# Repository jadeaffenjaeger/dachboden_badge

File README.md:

# Dachboden Robot Logo PCB badge

PCB Art badge using 2020 WS2812B SMD LEDs, attiny45 MCU and light_ws2812 library.

Detailed writeup can be found [here](https://etrommer.github.io/projects/electronics/2021/11/06/robot-badge.html)

## Programming

To build the firmware, you need the avr-gcc toolchain and a [USBtinyISP](https://learn.adafruit.com/usbtinyisp) (which you can buy for a few euros on AliExpress etc.)

```bash
cd firmware
make all
```
Then, with the programmer connected to the test points on the back of the badge, run:
```bash
make fuses
make program
```
to flash the firmware onto the badge.

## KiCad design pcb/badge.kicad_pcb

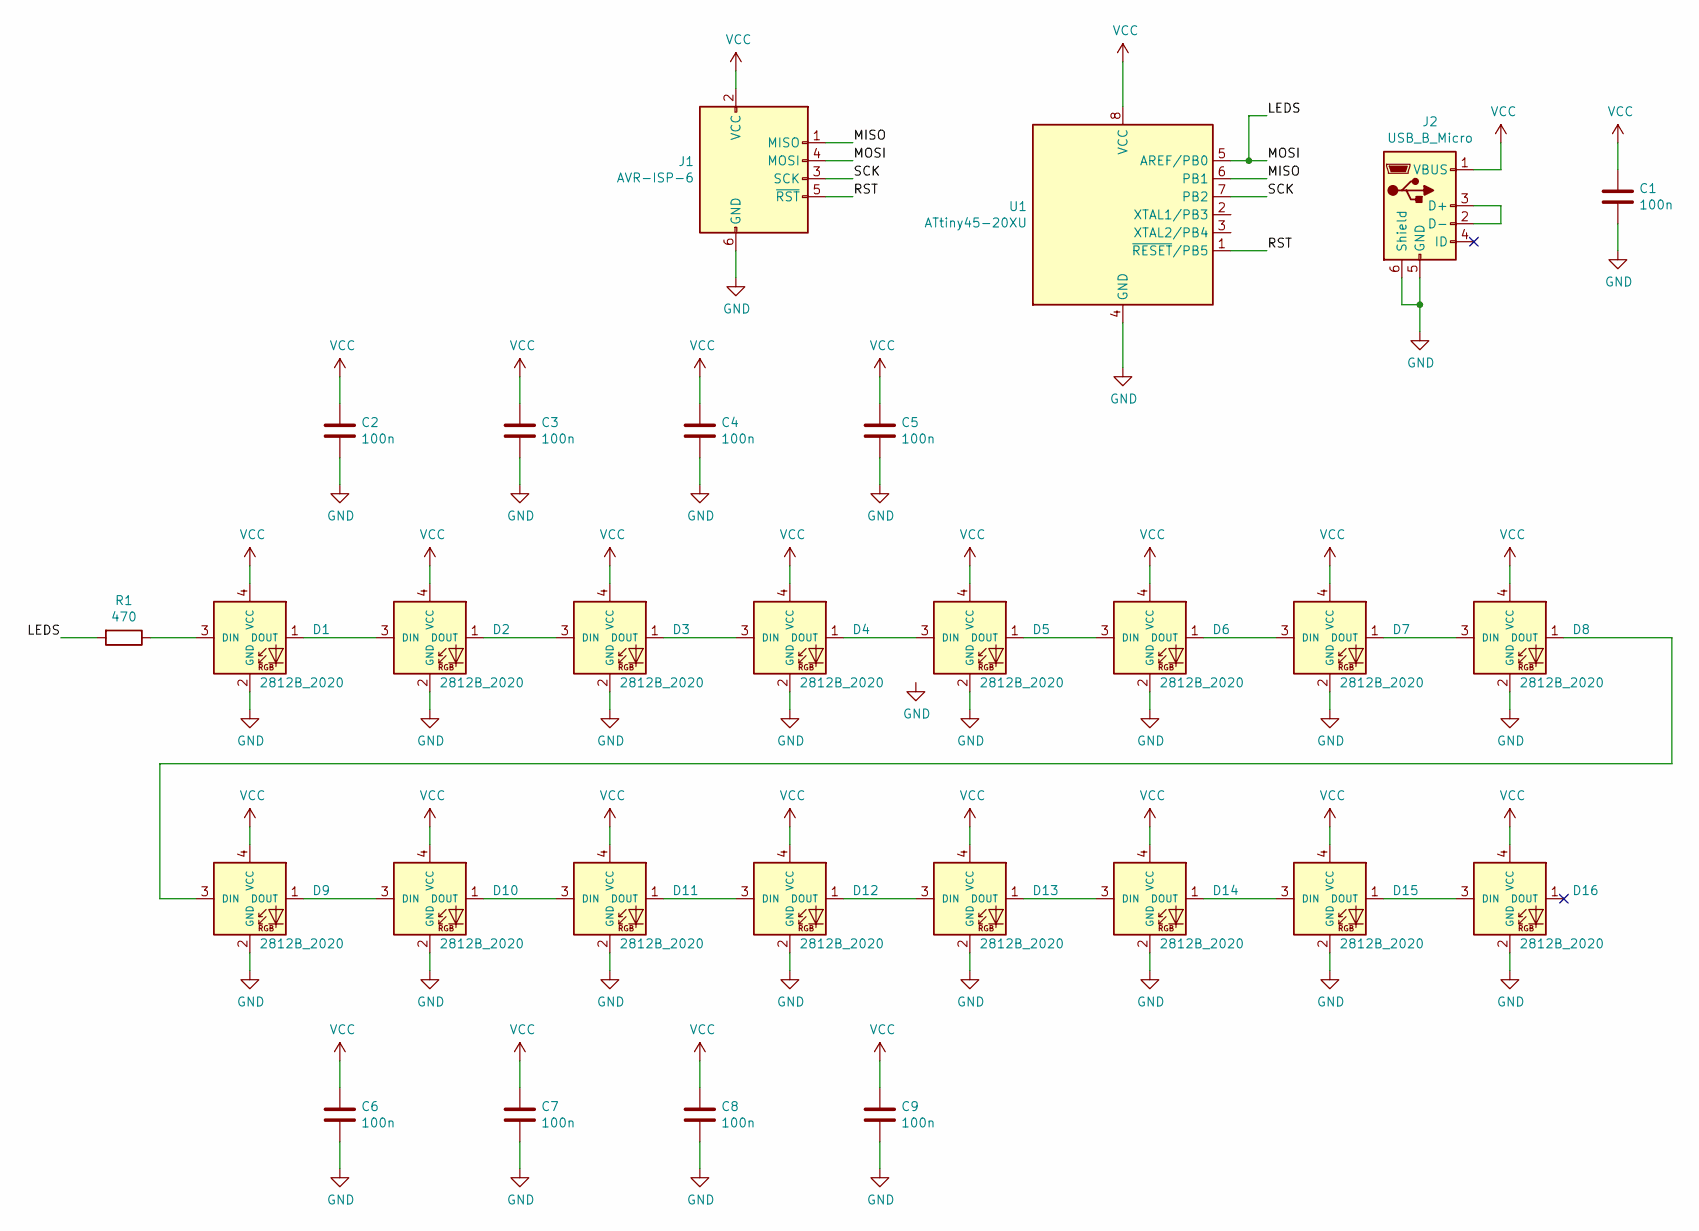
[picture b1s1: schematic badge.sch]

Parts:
C1, C2, C3, C4, C5, C6, C7, C8, C9: 100n; C_0402_1005Metric
D1, D2, D3, D4, D5, D6, D7, D8, D9, D10, D11, D12, D13, D14, D15, D16: 2812B_2020; ws2812_2020
J1: AVR-ISP-6; debug_header
J2: USB_B_Micro; micro_usb
R1: 470; R_0402_1005Metric
U1: ATtiny45-20XU; SOIJ-8_5.3x5.3mm_P1.27mm

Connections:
/LEDS: J1.4 (MOSI), R1.2, U1.5 (AREF/PB0)
/MISO: J1.1 (MISO), U1.6 (PB1)
/RST: J1.5 (~RST), U1.1 (~RESET~/PB5)
/SCK: J1.3 (SCK), U1.7 (PB2)
GND: C1.2, C2.2, C3.2, C4.2, C5.2, C6.2, C7.2, C8.2, C9.2, D1.2 (GND), D2.2 (GND), D3.2 (GND), D4.2 (GND), D5.2 (GND), D6.2 (GND), D7.2 (GND), D8.2 (GND), D9.2 (GND), D10.2 (GND), D11.2 (GND), D12.2 (GND), D13.2 (GND), D14.2 (GND), D15.2 (GND), D16.2 (GND), J1.6 (GND), J2.5 (GND), J2.6 (Shield), U1.4 (GND)
unnamed: D1.1 (DOUT), D2.3 (DIN)
unnamed: D1.3 (DIN), R1.1
unnamed: D2.1 (DOUT), D3.3 (DIN)
unnamed: D3.1 (DOUT), D4.3 (DIN)
unnamed: D4.1 (DOUT), D5.3 (DIN)
unnamed: D5.1 (DOUT), D6.3 (DIN)
unnamed: D6.1 (DOUT), D7.3 (DIN)
unnamed: D7.1 (DOUT), D8.3 (DIN)
unnamed: D8.1 (DOUT), D9.3 (DIN)
unnamed: D10.1 (DOUT), D11.3 (DIN)
unnamed: D9.1 (DOUT), D10.3 (DIN)
unnamed: D11.1 (DOUT), D12.3 (DIN)
unnamed: D12.1 (DOUT), D13.3 (DIN)
unnamed: D13.1 (DOUT), D14.3 (DIN)
unnamed: D14.1 (DOUT), D15.3 (DIN)
unnamed: D15.1 (DOUT), D16.3 (DIN)
unnamed: J2.2 (D-), J2.3 (D+)
VCC: C1.1, C2.1, C3.1, C4.1, C5.1, C6.1, C7.1, C8.1, C9.1, D1.4 (VCC), D2.4 (VCC), D3.4 (VCC), D4.4 (VCC), D5.4 (VCC), D6.4 (VCC), D7.4 (VCC), D8.4 (VCC), D9.4 (VCC), D10.4 (VCC), D11.4 (VCC), D12.4 (VCC), D13.4 (VCC), D14.4 (VCC), D15.4 (VCC), D16.4 (VCC), J1.2 (VCC), J2.1 (VBUS), U1.8 (VCC)

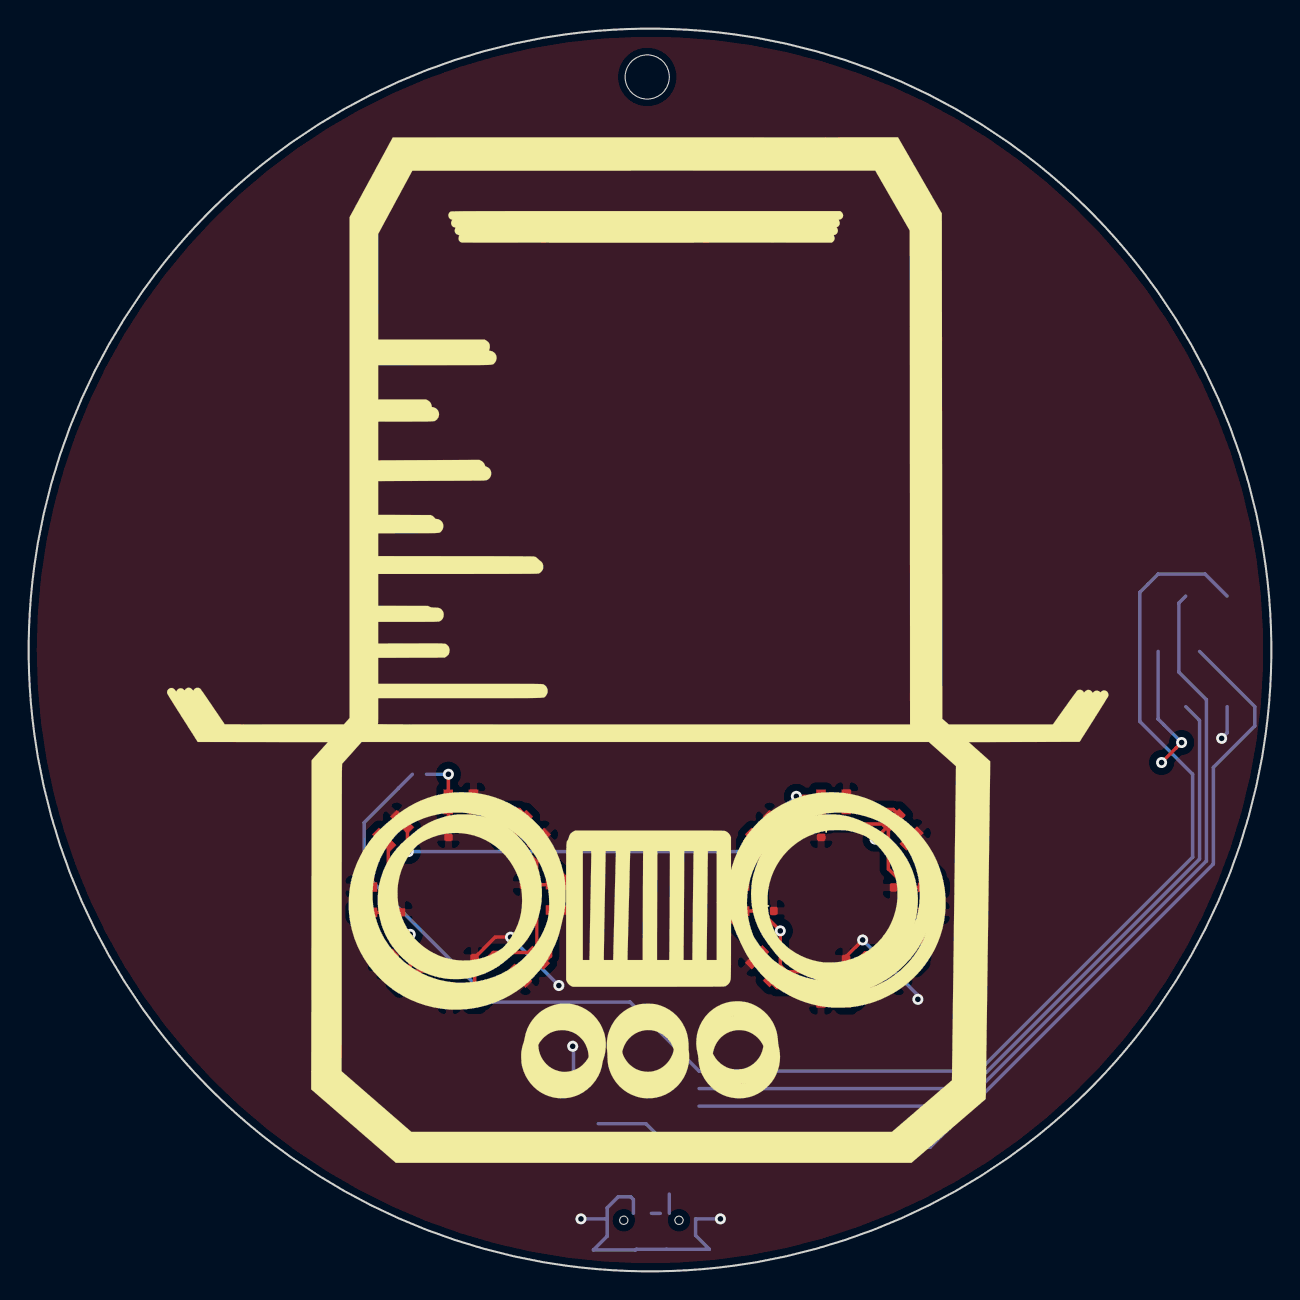
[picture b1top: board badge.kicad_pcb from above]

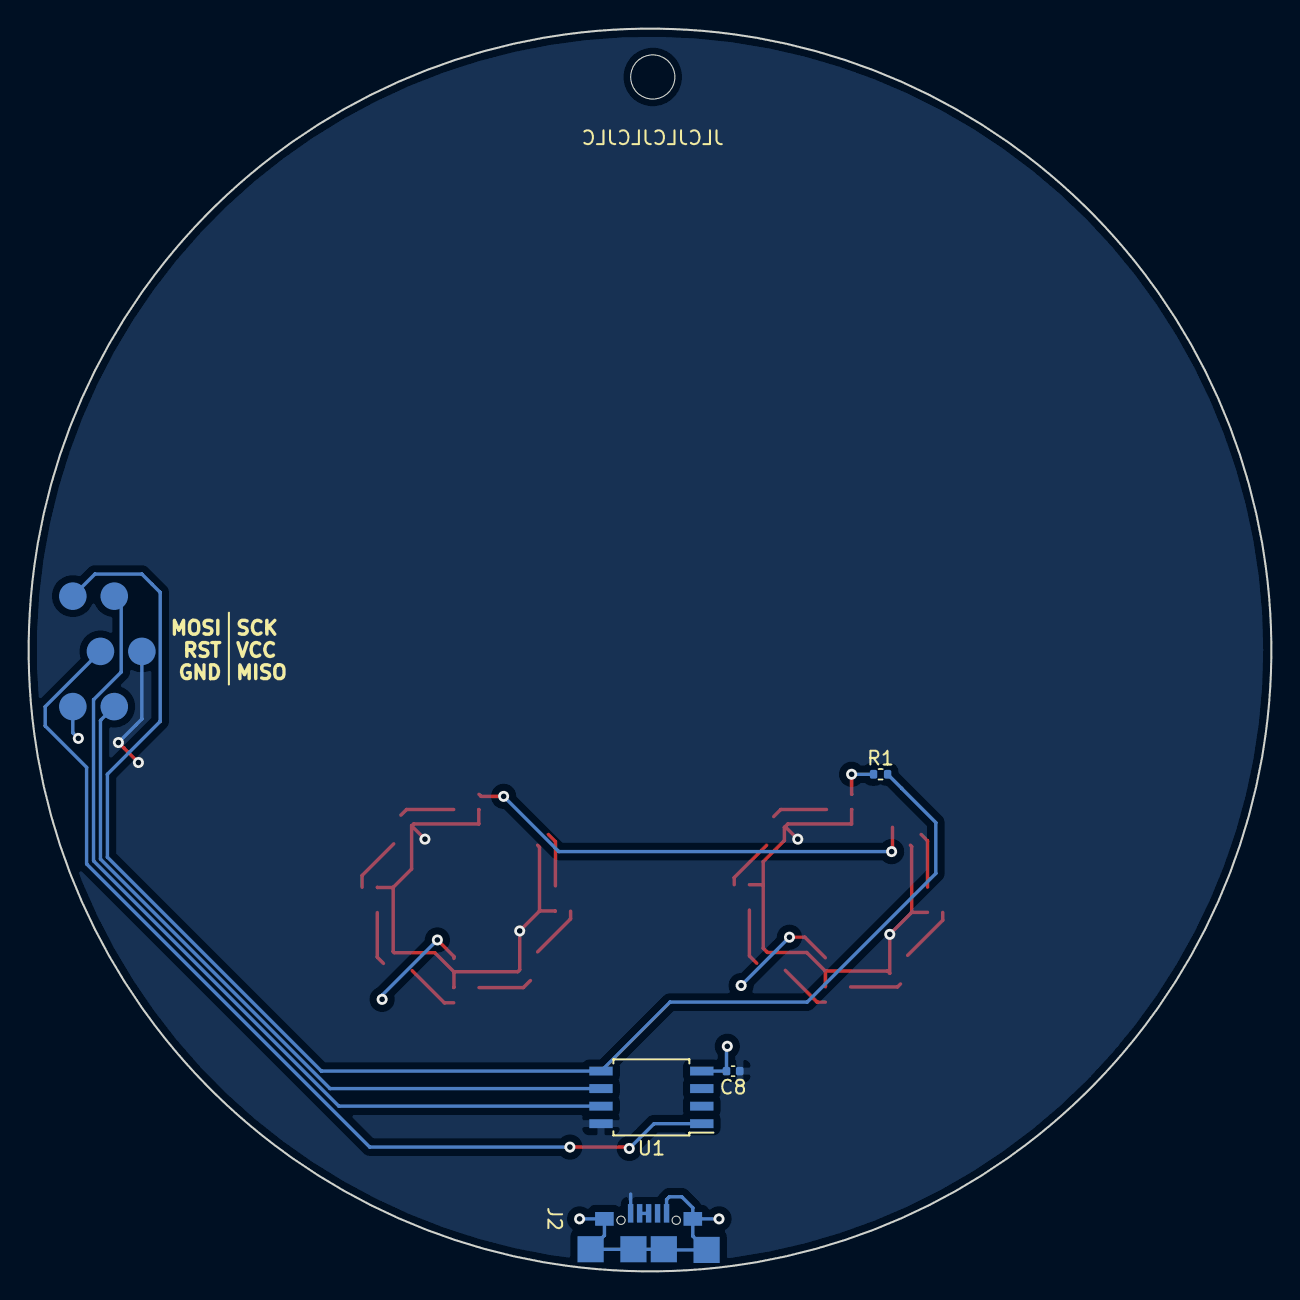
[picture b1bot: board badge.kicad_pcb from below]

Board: 2 copper layers, 90.0 x 90.0 mm, 30 parts (5 on the bottom side), 23 nets.

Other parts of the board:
Ref**: Val**; footprint

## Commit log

2022-01-02 Add PCB files
2022-01-02 Add firmware
2022-01-02 Add README
2022-01-02 Add badge picture
2022-01-03 Add animations and clean up comments
